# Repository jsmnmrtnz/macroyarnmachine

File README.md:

Hey!
How exciting you want to build the Macro Yarn Machine. I have built this machine as part of my Master’s project in 2024, and I would have never been able to build it without relying on published Open-Source Hardware projects and the community.

Therefor I want to credit:

1.) Circular Knitic by Varvara Guljajeva and Canet Sola, 2014. https://github.com/var-mar/circular_knitic

2.) HILO Spinning Machine. As I have been working with Sara Diaz Rodriguez closely for the past 2 years and learned about Open-Source Hardware for Textiles from her. https://www.hilotextiles.com/

If you want to credit my machine, please use:
„Macro Yarn Machine“ by Jasmin Martinez, 2024

further information:
Master Thesis: Martinez, Jasmin. Hacking Textile Tools. 2024. Kunsthochschule Weißensee (Weissensee Art Academy).
Mentored by Prof. Christiane Sauer and Prof. Dr. Lucy Norris.

Note: I reverse-documented building the machine, which should explain why the parts are full of soil and grease. Please excuse this and let me know if it makes anything unclear to you. Now – let’s start building!

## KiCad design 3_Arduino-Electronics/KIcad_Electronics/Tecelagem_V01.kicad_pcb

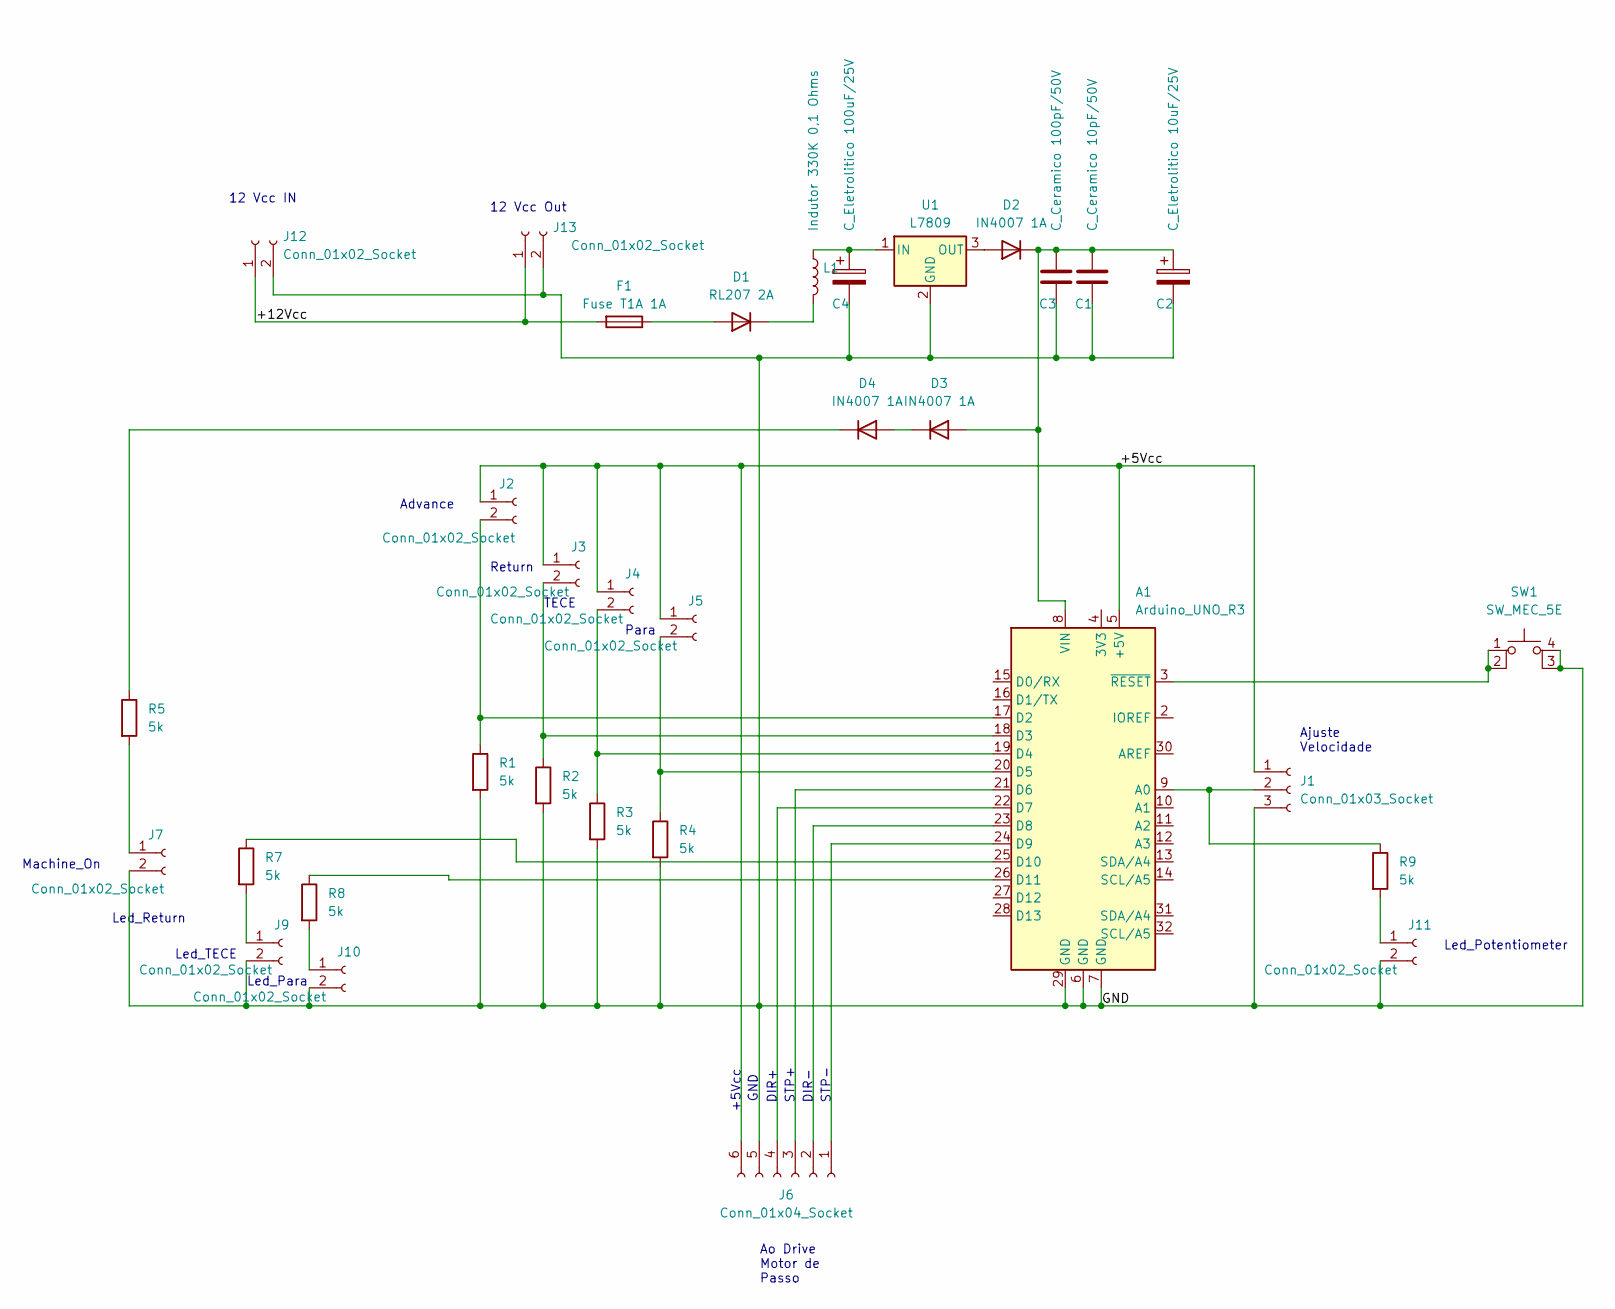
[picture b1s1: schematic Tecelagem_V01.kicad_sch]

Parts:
A1: Arduino_UNO_R3
C1: C_Ceramico 10pF/50V; C_Disc_D3.0mm_W1.6mm_P2.50mm
C2: C_Eletrolitico 10uF/25V; CP_Radial_D5.0mm_P2.50mm
C3: C_Ceramico 100pF/50V; C_Disc_D3.0mm_W1.6mm_P2.50mm
C4: C_Eletrolitico 100uF/25V; CP_Radial_D5.0mm_P2.50mm
D1: RL207 2A; D_DO-27_P5.08mm_Vertical_AnodeUp
D2, D3, D4: IN4007 1A; D_DO-15_P3.81mm_Vertical_AnodeUp
F1: Fuse T1A 1A; Fuse_Littelfuse_372_D8.50mm
J1: Conn_01x03_Socket; Molex_KK-254_AE-6410-03A_1x03_P2.54mm_Vertical
J2, J3, J4, J5, J7, J9, J10, J11: Conn_01x02_Socket; Molex_KK-254_AE-6410-02A_1x02_P2.54mm_Vertical
J6: Conn_01x04_Socket; Molex_KK-254_AE-6410-06A_1x06_P2.54mm_Vertical
J12, J13: Conn_01x02_Socket; Molex_KK-396_A-41791-0002_1x02_P3.96mm_Vertical
L1: Indutor 330K 0,1 Ohms; L_Radial_D7.8mm_P5.00mm_Fastron_07HCP
R1, R2, R3, R4, R5, R7, R8, R9: 5k; R_Axial_DIN0204_L3.6mm_D1.6mm_P1.90mm_Vertical
SW1: SW_MEC_5E; Tactil_6mm
U1: L7809; TO-126-3_Vertical

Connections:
/+5Vcc: A1.5 (+5V), J1.1, J2.1, J3.1, J4.1, J5.1, J6.6
/+12Vcc: F1.2, J12.1, J13.1
/GND: A1.6 (GND), A1.7 (GND), A1.29 (GND), C1.2, C2.2, C3.2, C4.2, J1.3, J6.5, J7.2, J9.2, J10.2, J11.2, J12.2, J13.2, R1.2, R2.2, R3.2, R4.2, SW1.3 (K), SW1.4 (A), U1.2 (GND)
unnamed: A1.9 (A0), J1.2, R9.1
unnamed: A1.17 (D2), J2.2, R1.1
unnamed: A1.18 (D3), J3.2, R2.1
unnamed: A1.19 (D4), J4.2, R3.1
unnamed: A1.20 (D5), J5.2, R4.1
unnamed: A1.21 (D6), J6.3
unnamed: A1.22 (D7), J6.4
unnamed: A1.23 (D8), J6.2
unnamed: A1.24 (D9), J6.1
unnamed: A1.25 (D10), R7.1
unnamed: A1.26 (D11), R8.1
unnamed: A1.8 (VIN), C1.1, C2.1, C3.1, D2.1 (K), D3.2 (A)
unnamed: A1.3 (~RESET), SW1.1, SW1.2
unnamed: D1.2 (A), F1.1
unnamed: D1.1 (K), L1.2
unnamed: D2.2 (A), U1.3 (OUT)
unnamed: D3.1 (K), D4.2 (A)
unnamed: D4.1 (K), R5.1
unnamed: J7.1, R5.2
unnamed: J9.1, R7.2
unnamed: J10.1, R8.2
unnamed: J11.1, R9.2
unnamed: C4.1, L1.1, U1.1 (IN)

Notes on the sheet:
Para
Led_Para
12 Vcc IN
TECE
Led_TECE
GND
Ajuste Velocidade
Led_Return
+5Vcc
Machine_On
Ao Drive Motor de Passo
Advance
12 Vcc Out
STP+
DIR-
Return
Led_Potentiometer
DIR+
STP-

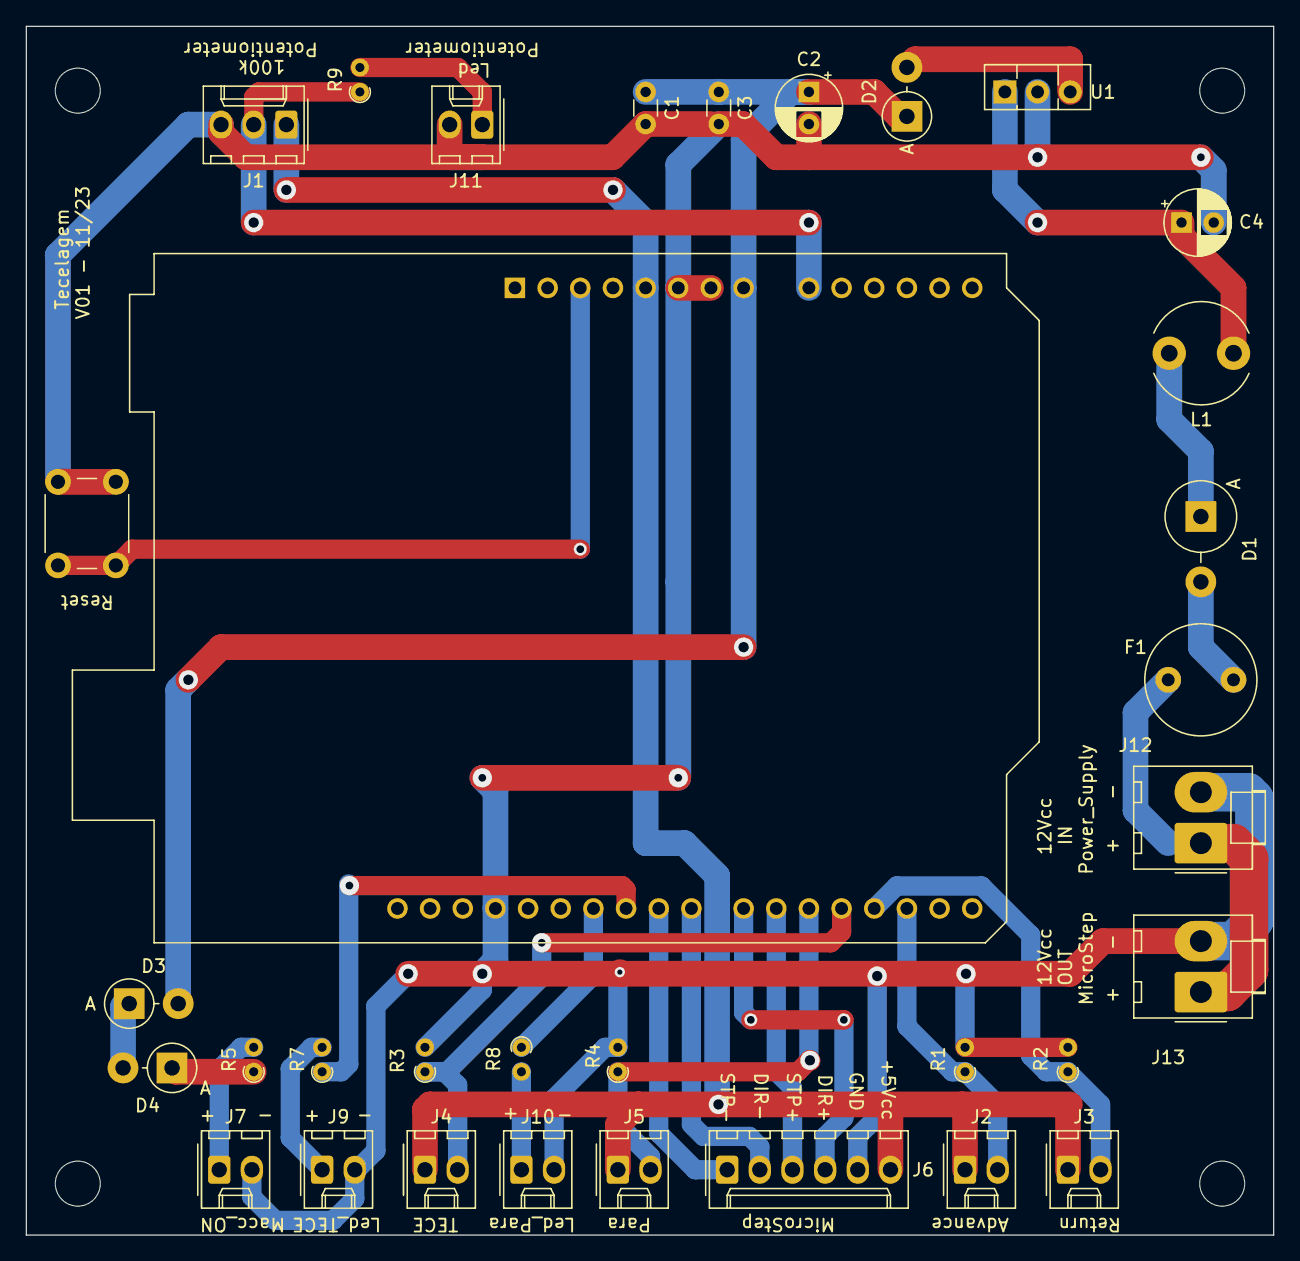
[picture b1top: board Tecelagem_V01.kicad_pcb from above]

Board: 2 copper layers, 97.0 x 94.0 mm, 33 parts (0 on the bottom side), 26 nets.

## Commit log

2025-01-21 added stls
2025-01-21 Create LICENSE
